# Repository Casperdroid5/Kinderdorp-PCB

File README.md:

# Kinderdorp PCB 👍

An interactive educational PCB designed for children to learn electronics through hands-on experimentation with LEDs, sensors, and programming.

## 📋 Overview

The Kinderdorp PCB is an ESP32-C3 based learning platform featuring addressable RGB LEDs, user input buttons, sensors, and multiple power options. The board includes fun visual elements and is designed to be both educational and engaging for young learners.

## ✨ Features

### 🎯 Core Components
- **ESP32-C3-WROOM-02-N4** microcontroller (4MB Flash)
- **8x WS2812B** addressable RGB LEDs arranged in a creative pattern
- **2x Tactile buttons** for user interaction
- **Light sensor (LDR)** for ambient light detection
- **Buzzer** for audio feedback
- **USB-C connector** for power and programming

### 🔋 Power Options
- **USB-C** power input (5V)
- **Dual CR2032** coin cell battery holders
- **3x AAA** battery pack option
- **AMS1117-3.3V** voltage regulator
- Battery voltage monitoring circuit

### 🔌 Connectivity
- **8-pin header** for expansion and prototyping
- **Programming pins** for development
- **Test points** for debugging

## 🔧 Technical Specifications

| Component | Specification |
|-----------|---------------|
| **Microcontroller** | ESP32-C3-WROOM-02-N4 (4MB) |
| **Operating Voltage** | 3.3V |
| **Power Input** | 5V via USB-C or 3-6V battery |
| **LEDs** | 8x WS2812B RGB (5050 package) |
| **Buttons** | 2x DTSM-61R tactile switches |
| **Buzzer** | KSSGK4B16-20 |
| **Light Sensor** | LDR07 photoresistor |
| **PCB Dimensions** | ~100mm x 100mm |

## 📍 Pin Mapping

### GPIO Assignments
```
GPIO0  - Programming/Boot button
GPIO1  - UART TX (programming)
GPIO3  - UART RX (programming)  
GPIO4  - User Button 1
GPIO5  - RGB LED Data Out
GPIO6  - SDA (I2C)
GPIO7  - SCL (I2C)
GPIO8  - User Button 2
GPIO9  - Buzzer Control
GPIO10 - Light Sensor (ADC)
GPIO18 - Battery Voltage Monitor
GPIO19 - RGB LED Data In
```

### LED Chain Order
The 8 WS2812B LEDs are connected in series:
`LED1 → LED2 → LED3 → LED4 → LED5 → LED6 → LED7 → LED8`

## 🚀 Getting Started

### Prerequisites
- **Arduino IDE** or **PlatformIO**
- **ESP32 board package** installed
- **FastLED** or **Adafruit NeoPixel** library for LED control

### Hardware Setup
1. **Power the board** via USB-C or install batteries
2. **Connect** USE the breakout pads USB+ and USB- or UART to program the board
3. **Install** any additional components if using expansion header

### Basic Programming Example

```cpp
#include <FastLED.h>

#define LED_PIN 19
#define NUM_LEDS 8
#define BUTTON1_PIN 4
#define BUTTON2_PIN 8
#define BUZZER_PIN 9
#define LDR_PIN 10

CRGB leds[NUM_LEDS];

void setup() {
  FastLED.addLeds<WS2812B, LED_PIN, GRB>(leds, NUM_LEDS);
  pinMode(BUTTON1_PIN, INPUT_PULLUP);
  pinMode(BUTTON2_PIN, INPUT_PULLUP);
  pinMode(BUZZER_PIN, OUTPUT);
}

void loop() {
  // Rainbow effect
  for(int i = 0; i < NUM_LEDS; i++) {
    leds[i] = CHSV(i * 32, 255, 255);
  }
  FastLED.show();
  delay(100);
}
```

## 🎓 Educational Applications

### Beginner Projects
- **LED Patterns** - Create colorful light sequences
- **Button Response** - Interactive games with button presses
- **Light Detection** - Automatic brightness control
- **Sound Effects** - Musical patterns with the buzzer

### Intermediate Projects
- **Simon Says Game** - Memory game using LEDs and buttons
- **Light Meter** - Display ambient light levels
- **Digital Pet** - Virtual pet with LED expressions
- **Alarm Clock** - Wake-up light with buzzer

### Advanced Projects
- **WiFi Connectivity** - IoT integration and remote control
- **Sensor Dashboard** - Environmental monitoring
- **Interactive Art** - Motion-responsive installations
- **Educational Games** - Programming challenges

## 🔋 Power Management

### Battery Life Optimization
- Use **deep sleep mode** when inactive
- **Dim LEDs** or turn off when not needed
- **Monitor battery voltage** (GPIO18) for low battery warnings

### Battery Voltage Monitoring
```cpp
float getBatteryVoltage() {
  int rawValue = analogRead(18);
  // Voltage divider: 6V→3V, 4.5V→2.25V, 3V→1.5V, 2V→1V
  return (rawValue / 4095.0) * 3.3 * 2.0;
}
```

## 🛠️ Assembly Notes

### Battery Installation
- **Option 1**: Install 2x CR2032 coin cells in BT1 and BT2
- **Option 2**: Connect 3x AAA battery pack to BATTPACK1
- **Do not** install both battery options simultaneously (should not be possible if PCB is asssembled correctly)

## 🎨 Design Features

The PCB includes playful design elements:
- **Artistic patterns** and decorative silkscreen
- **Child-friendly** component layout
- **Clear labeling** for educational purposes
- **Robust construction** for classroom use

## 📄 License

This project is released under the [MIT License](LICENSE). Feel free to use, modify, and distribute for educational purposes.

## 👨‍💻 Author

**Casper R. Tak**

---

*Kinderdorp PCB - Making electronics fun and accessible for young (and older) minds! 🌟*

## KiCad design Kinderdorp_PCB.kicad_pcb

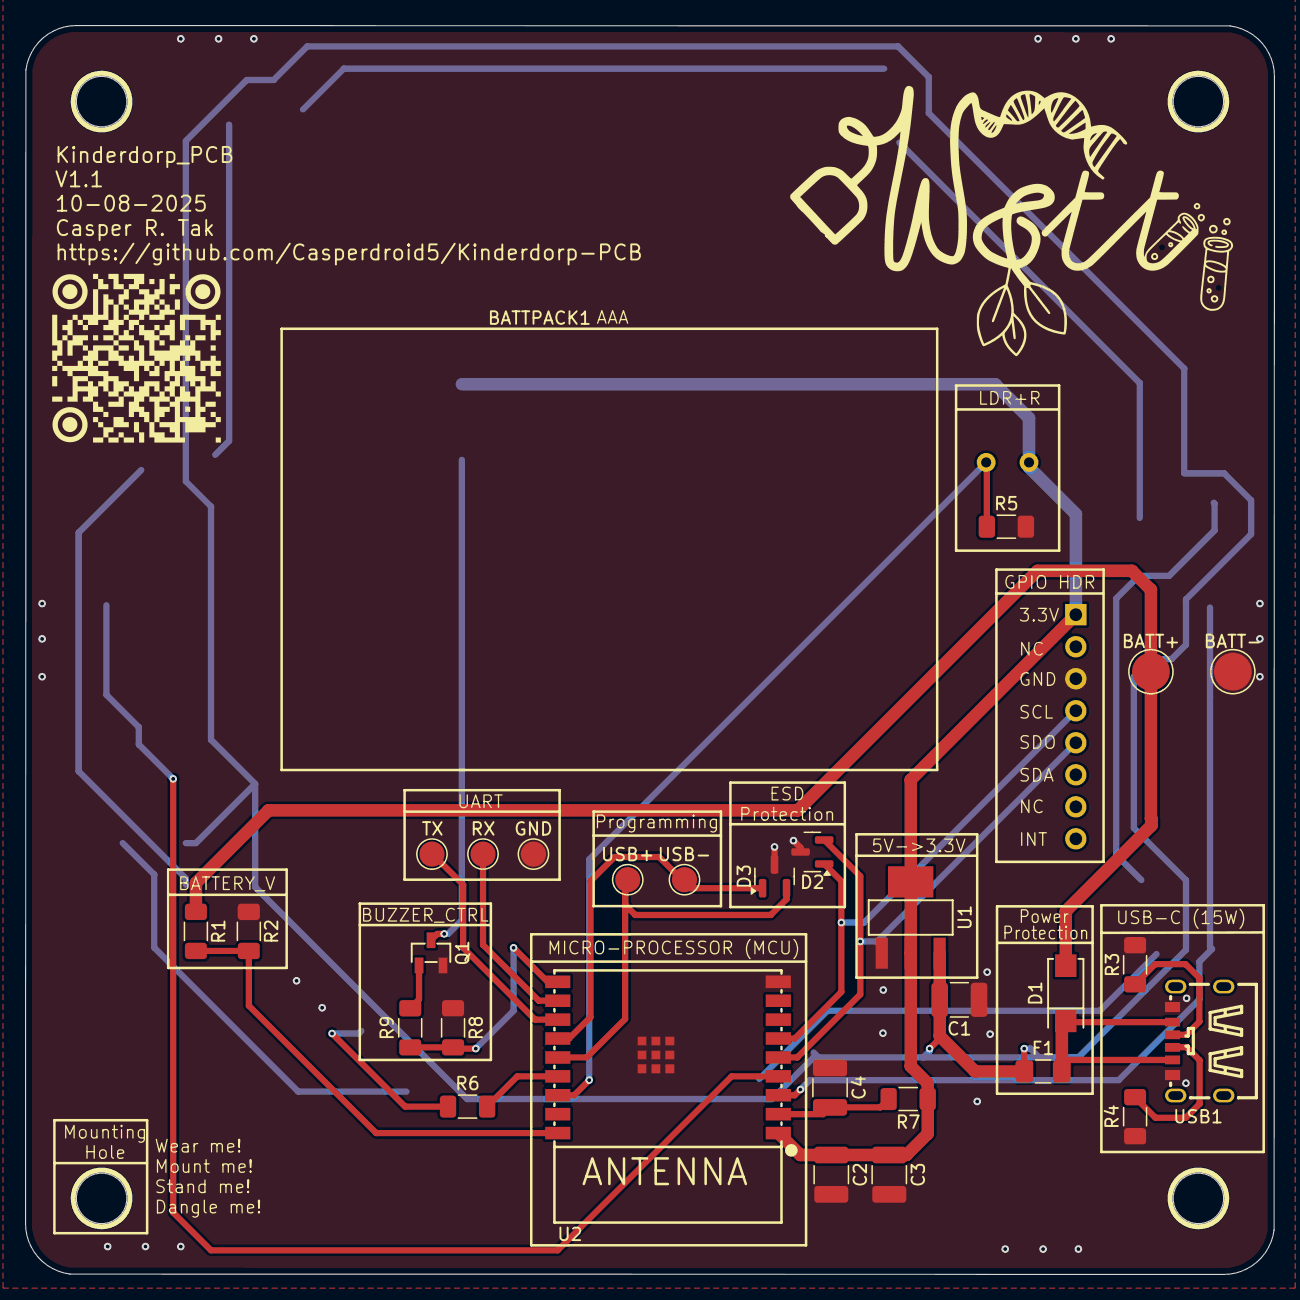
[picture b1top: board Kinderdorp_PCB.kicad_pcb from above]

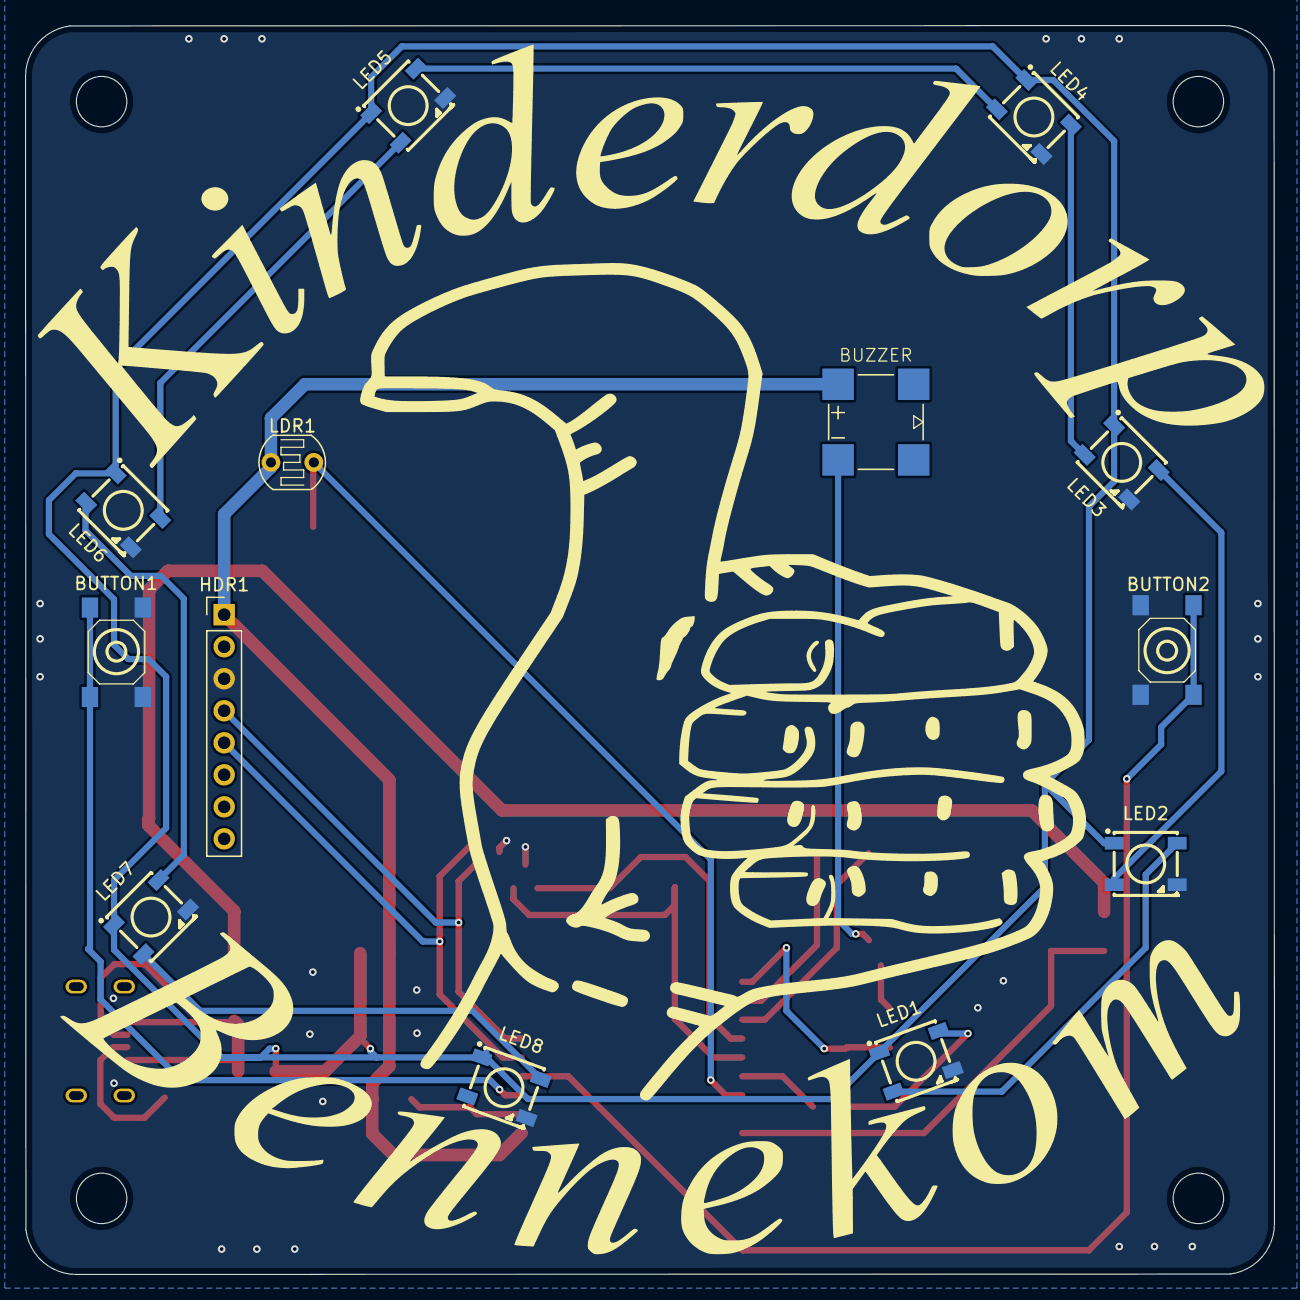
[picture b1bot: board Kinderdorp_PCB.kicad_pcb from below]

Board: 2 copper layers, 99.1 x 99.1 mm, 42 parts (13 on the bottom side), 30 nets.

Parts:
BATT+: TestPoint_Pad_D3.0mm
BATT-: TestPoint_Alt; TestPoint_Pad_D3.0mm
BATTPACK1: Batteryplaceholder; MountingHole_2.1mm
BUTTON1, BUTTON2: DTSM-61R-V-T/R; KEY-SMD_4P-L6.2-W6.2-P4.50-LS9.0
C1, C3: 47uF 10V; C_1210_3225Metric_Pad1.33x2.70mm_HandSolder
C2: 100nF 50V; C_1210_3225Metric_Pad1.33x2.70mm_HandSolder
C4: 10uF 25V; C_1210_3225Metric_Pad1.33x2.70mm_HandSolder
D1: 1N5819_C437199; SMA_L4.4-W2.6-LS5.0-RD
D2, D3: SM712_SOT23; SOT-23
F1: Resetable fuse 0.75A; Fuse_1206_3216Metric_Pad1.42x1.75mm_HandSolder
GND: TestPoint_Probe; TestPoint_Pad_D2.0mm
HDR1: Conn_01x08; PinHeader_1x08_P2.54mm_Vertical
LDR1: LDR07; R_LDR_5.1x4.3mm_P3.4mm_Vertical
LED1, LED2, LED3, LED4, LED5, LED6, LED7, LED8: WS2812B; LED-SMD_4P-L5.0-W5.0-BL_TC5050RGB
LS1: KSSGK4B16-20
Q1: 2N7002_C306856; SOT-23-3_L2.9-W1.3-P1.90-LS2.4-BR
R1, R2, R7, R8: 10k; R_1206_3216Metric_Pad1.30x1.75mm_HandSolder
R3, R4: 5k1; R_1206_3216Metric_Pad1.30x1.75mm_HandSolder
R5: 5k; R_1206_3216Metric_Pad1.30x1.75mm_HandSolder
R6: 200; R_1206_3216Metric_Pad1.30x1.75mm_HandSolder
R9: 100; R_1206_3216Metric_Pad1.30x1.75mm_HandSolder
RX: TestPoint_Probe; TestPoint_Pad_D2.0mm
TX: TestPoint_Probe; TestPoint_Pad_D2.0mm
U1: AMS1117-3.3_C347222; SOT-223-4_L6.5-W3.5-P2.30-LS7.0-BR
U2: ESP32-C3-WROOM-02-N4(4MB); BULETM-SMD_ESPRESSIF_ESP32-C3-WROOM-02-N4-4MB
USB1: TYPE-C 6P(073); TYPE-C-SMD_TYPE-C-6P_5
USB+: TestPoint_Probe; TestPoint_Pad_D2.0mm
USB-: TestPoint_Probe; TestPoint_Pad_D2.0mm

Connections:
+3V3: C2.1, C3.2, HDR1.1, LDR1.1, LS1.P, R7.1, U1.2 (VOUT(TAB)), U1.4 (TAB), U2.1 (3V3)
+5V: C1.2, F1.1, LED1.1 (VDD), LED2.1 (VDD), LED3.1 (VDD), LED4.1 (VDD), LED5.1 (VDD), LED6.1 (VDD), LED7.1 (VDD), LED8.1 (VDD), U1.3 (VIN)
BATT_V: R1.2, R2.1, U2.18 (IO0)
BUZZ: R8.2, R9.1, U2.10 (IO10)
D+_USB: D3.2 (A2), U2.14 (IO19), USB+.1
D-_USB: D3.1 (A1), U2.13 (IO18), USB-.1
ESP_EN: C4.2, R7.2, U2.2 (EN)
GND: BATT-.1, BUTTON1.2, BUTTON1.4, BUTTON2.2, BUTTON2.4, C1.1, C2.2, C3.1, C4.1, D2.3 (common), D3.3 (common), GND.1, HDR1.3, LED1.3 (VSS), LED2.3 (VSS), LED3.3 (VSS), LED4.3 (VSS), LED5.3 (VSS), LED6.3 (VSS), LED7.3 (VSS), LED8.3 (VSS), Q1.2 (S), R2.2, R3.1, R4.1, R5.2, R8.1, U1.1 (ADJ(GND)), U2.9 (GND), U2.19 (EP), USB1.A12 (GND), USB1.B12 (GND)
GPIO3: R6.2, U2.15 (IO3)
GPIO4: BUTTON1.1, BUTTON1.3, U2.3 (IO4)
GPIO5: BUTTON2.1, BUTTON2.3, U2.4 (IO5)
GPIO6: D2.2 (A2), HDR1.5, U2.5 (IO6)
GPIO7: D2.1 (A1), HDR1.4, U2.6 (IO7)
unnamed: BATT+.1, D1.2 (A), R1.1
unnamed: D1.1 (C), F1.2, USB1.A9 (VBUS), USB1.B9 (VBUS)
unnamed: LED1.4 (DIN), R6.1
unnamed: LED1.2 (DOUT), LED2.4 (DIN)
unnamed: LED2.2 (DOUT), LED3.4 (DIN)
unnamed: LED3.2 (DOUT), LED4.4 (DIN)
unnamed: LED4.2 (DOUT), LED5.4 (DIN)
unnamed: LED5.2 (DOUT), LED6.4 (DIN)
unnamed: LED6.2 (DOUT), LED7.4 (DIN)
unnamed: LED7.2 (DOUT), LED8.4 (DIN)
unnamed: LS1.N, Q1.3 (D)
unnamed: Q1.1 (G), R9.2
unnamed: LDR1.2, R5.1, U2.16 (IO2)
unnamed: RX.1, U2.11 (RXD)
unnamed: TX.1, U2.12 (TXD)
unnamed: R4.2, USB1.A5 (CC1)
unnamed: R3.2, USB1.B5 (CC2)

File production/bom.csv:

Designator,Footprint,Quantity,Value,LCSC Part #
BATT+,TestPoint_Pad_D3.0mm,1,~,
BATT-,TestPoint_Pad_D3.0mm,1,TestPoint_Alt,
"BT1:, BT2:",BAT-SMD_MY-2032-12,2,MY-2032-12,C964833
"BUTTON1, BUTTON2",KEY-SMD_4P-L6.2-W6.2-P4.50-LS9.0,2,DTSM-61R-V-T/R,C224977
"C1, C3",1210,2,47uF 10V,
C2,1210,1,100nF 50V,
C4,1210,1,10uF 25V,
D1,SMA_L4.4-W2.6-LS5.0-RD,1,1N5819_C437199,C437199
"D2, D3",SOT-23,2,SM712_SOT23,
F1,1206,1,Fuse_Small 2A,
"GND, RXD, TXD, USB+, USB-",TestPoint_Pad_D2.0mm,5,TestPoint_Probe,
HDR1,PinHeader_1x08_P2.54mm_Vertical,1,Conn_01x08,
LDR1,R_LDR_5.1x4.3mm_P3.4mm_Vertical,1,LDR07,
"LED1, LED2, LED3, LED4, LED5, LED6, LED7, LED8",LED-SMD_4P-L5.0-W5.0-BL_TC5050RGB,8,WS2812B,
LS1,KSSGK4B16-20,1,KSSGK4B16-20,
Q1,SOT-23-3_L2.9-W1.3-P1.90-LS2.4-BR,1,2N7002_C306856,
"R1, R2, R7, R8",1206,4,10k,
"R3, R4",1206,2,5k1,
R5,1206,1,5k,
"R6, R9",1206,2,200,
U1,SOT-223-4_L6.5-W3.5-P2.30-LS7.0-BR,1,AMS1117-3.3_C347222,C347222
U2,BULETM-SMD_ESPRESSIF_ESP32-C3-WROOM-02-N4-4MB,1,ESP32-C3-WROOM-02-N4(4MB),
USB1,TYPE-C-SMD_TYPE-C-6P_5,1,TYPE-C 6P(073),C668623

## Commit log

2025-05-12 updated all 3d models
2025-05-12 removed backups folder
2025-05-12 added AAA box 3d model and reference images
2025-05-12 imported/created thumb design
2025-07-26 created new oultine for pcb
2025-07-26 fixed naming designators
2025-07-26 fixed annotation again
2025-07-26 finished layout
2025-07-26 updated logo
2025-07-26 saving changes to W&T logo
2025-07-26 routing
2025-07-26 added media files and finished routing
2025-07-26 cleanup
2025-07-27 Finalized design
    - added esd protection
    - minor silkscreen improvements
2025-07-27 minor changes to files and added production files
2025-07-27 updated silkscreen
2025-07-27 made some more change to silkscreen
    (because of my borderline OCD)
2025-07-27 moved board to centre
2025-08-07 Working on software for the PCB
2025-08-07 Working on Kinderdorp song melody
2025-08-07 working on the tedious task of making the song
2025-08-08 working on kinderlied song
2025-08-08 added pitches.h and happy birthday
2025-08-08 Manual song creation in arduino and added audio files
2025-08-08 more musical improvements
2025-08-08 FIxed end of song
2025-08-09 More song improvements
2025-08-09 Song V1 completed
2025-08-09 fixed button design error
2025-08-10 added song to seperate files
2025-08-10 added more lighting effects and updated i2c on pcb (header)
2025-08-10 V1.0 of code
    - music
    - light effects
    - serial monitor
    - battery detection
2025-08-10 ldr updated and memmory added
2025-08-10 updated PCB to V1.1
    removed cr2032 (this is not viable with the current draw of the board)
